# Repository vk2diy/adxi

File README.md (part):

# adxi - ADX Improved

[ADX](https://github.com/WB2CBA/ADX) is an abbreviation for Arduino Digital Xceiver, a project emphasizing simplicity and Arduino hardware creating a [direct-conversion receiver](https://en.wikipedia.org/wiki/Direct-conversion_receiver) focused on [digital modes](http://www.arrl.org/digital-data-modes).

The ADX project was based upon firmware by [JE1RAV](https://github.com/je1rav/QP-7C) extending on original work by Burkhard Kainka (DK7JD) ([original German](https://www.elektronik-labor.de/HF/FT8QRP.html), [English translation](https://www-elektronik--labor-de.translate.goog/HF/FT8QRP.html?_x_tr_sl=auto&_x_tr_tl=en&_x_tr_hl=en-US&_x_tr_pto=wapp)).

This (very distant!) fork of ADX is called __adxi__ (or "ADX Improved") with the following major changes:
 * __abandon simplicity as a design philosophy__ since it limits our feature set and understanding
 * __improved design documentation__ to facilitate learning
 * __restores access to the project for modern KiCad__
 * __integrate known bug fixes__
 * __operates from a single USB-C cable__ replacing the need for an MCU programming cable, a power cable, an audio input cable, an audio output cable, and a host computer sound card.
 * __USB-C power supply__
 * __full computer control__ (remove buttons/blinkenlights interface)
 * __improved filtering__
 * __SWR, forward power and reverse power metering__ for debugging, safety and performance analysis
 * __supports more amateur bands__: 70cm/2m/10m/15m/17m/20m/30m/40m/60m/80m/160m/630m/2200m
 * __use of modern surface mount components__ for repeatability
 * __using platformio__ to manage the firmware build and dependencies in a modern way

## Other projects
 * Same MCU
   * [ADX](https://github.com/WB2CBA/ADX) ($? / ATMega328P based / multiple bands with effort / LED blinkenlights/ CD2003GP direct conversion receiver)
   * [(tr)uSDX](https://dl2man.de/) (PE1NNZ and DL2MAN) ($50 / ATMega328P based / multiple bands with effort / small OLED / direct sampling)
     * Based on [µSDX](https://github.com/threeme3/usdx)
 * Fancy-pants MCU
   * [sbitx](https://github.com/afarhan/sbitx) ($150+ / RPi4 based / 8 bands preconfigured / large OLED) ([documentation](https://www.sbitx.net/), [designer website](https://www.hfsignals.com/index.php/sbitx-v3/)) (newer zbitx)
 * Discussion
   * [ucx discussion group](https://groups.io/g/ucx)

## Project scope

The project scope generally includes the following:
 * Main board
 * Late stage board modules (each for different frequency bands)
 * Assembly information
 * Design documentation
 * Debugging documentation

## Current status of this fork

The first boards have been received and despite issues have been verified as partly functional.

Completed:

 - [x] Updated schematic (Kicad 8)
 - [x] Layout
 - [x] Late stage module interface design
 - [x] Design and layout of first late stage module 
 - [x] Firmware building correctly under platformio
 - [x] Final design review
 - [x] Order boards

Underway:

 - [x] Board testing and bringup
   - [x] USB hub verified
   - [x] USB audio verified
   - [x] USB MCU module passthru verified
   - [x] Power stage testing completed (issues found; resolution proposed and partly bench tested)
     - [x] Design and order power stage fix board
     - [x] Receive and assemble power stage fix board
     - [x] Debug power stages with fix board
   - [x] Assemble, solder-configure and mount late stage module
   - [ ] Firmware authoring to verify remaining functional blocks (in progress)
   - [ ] WSJT software integration testing (in progress)
 - [ ] Test late stage module
 - [ ] Verify overall system functionality
 - [ ] adxi-1.3 main board revision - incorporating power stage fixes and other improvements.
   - [x] Created new board tree

## Update (2025-01-27)

 * Started on looking at the late stage module (LSM) board.
 * Isolated 40M band LPF on a new board by cutting the trace from the impedance matching.
 * Instrumented both sides with NanoVNA but did not get expected results from the 7th order Butterworth approximation with values produced by [classe2-calculator](https://github.com/vk2diy/classe2-calculator), namely:
   * Command line: `./classe2 -p 5 -v 12 -b 40m -t infinite --l1 7.755uh -m SI2304DDS`
     * ie. Power 5W, voltage 12V, band 40m, type infinite, Class E L1 value 7.755uH, MOSFET SI2304DDS.
   * Output for precise configuration (not used): `7th = (0.23% error, 18 parts): C1_lpf=132.00pF (220.00pF || 330.00pF) L1_lpf=0.93µH (2.2µH || 2.7µH || 3.9µH) C2_lpf=536.00pF (33.00pF + 33.00pF + 470.00pF) L2_lpf=1.5µH (2.7µH || 3.3µH) C3_lpf=536.00pF (33.00pF + 33.00pF + 470.00pF) L3_lpf=0.93µH (2.2µH || 2.7µH || 3.9µH) C4_lpf=132.00pF (220.00pF || 330.00pF)`
   * Output for approximation configuration (used): `7th ≈ (13.57% error, 7 parts): C1_lpf=150.00pF L1_lpf=1µH C2_lpf=470.00pF L2_lpf=1.5µH C3_lpf=470.00pF L3_lpf=1µH C4_lpf=150.00pF`
 * I had expected to see a rapid falloff at a specific frequency, like this modeled version: 
 * However, instead I obtained very different results.
   * __Test setup__. I did try to test with the extra ground cable shown with a red X, but removed it (ground loop). No substantial change.  
   * __Test result__. This remained fairly constant in all test configurations (with and without termination resistors, various ground configurations). 
     * What we can see here is:
       * __S21 Logmag__ in yellow (~"through signal attenuation") shows a downward slope within the target band (marker location) before a flat response through around 13MHz at which it begins to taper off fairly steeply until 17MHz at which point it begins to climb again.
         * Our expectation would have been "falling off a cliff" after the filter cutoff frequency and not recovering until very high frequencies due to self-resonance of individual components.
         * This is a head scratcher.
       * __S21 Q10__ in green (~"resonance or energy storage potential") is an undesirable feature in a low pass filter. However, we can see significant Q values around 5MHz and 9MHz.
         * This would seem to indicate there is a source of resonance within the test circuit which we have not identified. However, without other points of comparison it may be hard to determine how abnormal this is.
       * __S21 Rsh__ in cyan (~"shunt resistance") exhibits a small peak around the target frequency but is otherwise flat.
       * __S21 Phase__ in magenta (~"phase angle") shows the target frequency band exists within the middle of a smooth phase cycle. There is no information in this to suggest an issue. However, it is notable that the phase shifts at 13MHz where we see the attenuation increase markedly. From prior experience it is common and expected for phase change to align with the end of designed frequency ranges.
   * __Broader result__. This shows markers for the 40m as well as 30m and 20m bands. You can see the attenuation restores rather than decays with increasing frequency after 17MHz, which is unexpected.  
   * __Final test setup__. Note cut trace, solder points and 47 ohm series resistors at either end. No substantial difference. 
 * I am as yet uncertain why this is.
   * Hypothesis: Incorrect impedance matching.
     * Determination: Invalid. Added 47Ω resistors either site of the LPF DUT with no substantial difference observed.
   * Hypothesis: Low SRF components.
     * Determination: Invalid. All components in the filter, both small capacitors and inductors should have higher SRFs, at least in the 100-200M+ range at a minimum. However, they are not reported in the datasheet as they are not high end components. Even with low end assumptions this should provide a safe 'order of magnitude' (<10M vs 100M+) buffer.
   * Hypothesis: Poor grounding.
     * Determination: Possible but unlikely. Connecting the ground at both ends of the DUT (ie. ground loop) causes no significant shift in the VNA output, versus just one end.
   * Hypothesis: Poor calibration.
     * Determination: Used a range of new calibrations, stored calibrations and recalibrations but in no case did this alter the general frequency response.
 * __Next steps__
   * I put it away and will come back to it another day to look at the 30M and 20M LPFs - hopefully one of them works!
   * I could try adding a solid ground plane just to see the difference.
   * I could try fabricating a range of physically separate filters as standalone PCBs to simplify debugging (no test points and cutting traces is a real pain).

## Update (2025-01-19)

 * Been awhile since an update, but haven't been idle.
 * [Built, tuned and tested a 20m/30m/40m fan dipole antenna](doc/antennas/20m-30m-40m-fan-dipole) and got this running with an RTLSDR as a reference point in order to support further testing. Despite being barely 1.5m off the ground and threaded through foliage, it works! Signals have been received from most continents already. 
 * Updated test plan:
   - [x] Antenna system
     - [x] Build or acquire a viable antenna
     - [x] Verify with NanoVNA and attenuator for protection
     - [x] Verify with other radio hardware
   - [ ] The power amplifier
     * Power amplifier low pass filter, matching network and resonator
       * NanoVNA between the band-specific solder bridges (fresh board, none soldered closed)
     * RF choke
       * NanoVNA between the `PA-SUPPLY` and the nearby solder bridges (fresh board, none soldered closed)
   - [ ] MCU power amplifier drive PWM signal
     * Instrument appropriately with scope then test with custom firmware
   - [ ] MCU receive enable signal
     * Instrument appropriately with scope then test with custom firmware
   - [ ] The demodulator chip
     * Verify configuration straps with scope
     * Verify expected input signal is present with scope
     * Verify output signal is present with scope
   - [ ] The USB sound chip
     * Verify configuration straps and/or MCU control lines
     * Verify input from demodulator and channel mixing is present
     * Monitor computer audio through regular audio software
     * Try creating static if necessary by shorting low voltage leads
     * Verify static comes through to computer audio software

## Update (2024-12-04)
 * [Proposed test plan](kicad-pcbs/adxi/README.md) for resolving current state focused on iterative verification

## Update (2024-11-25)

 * Researched Linux-based serial data capture solutions with an eye toward [Wireshark](https://www.wireshark.org/) (which my brain still calls *Ethereal*!) and hit on [socat](http://www.dest-unreach.org/socat/), which is a spiritual successor to Hobbit's [netcat](https://sectools.org/tool/netcat/) that talks serial in addition to TCP/UDP and should therefore do the job.
   * It seems [very closely aligned functionality for logging devices under control by other programs was added in or before 2021](https://news.ycombinator.com/item?id=26604002)
   * To date I have been attempting to manually interact with the firmware using [minicom](https://salsa.debian.org/minicom-team/minicom) which is tedious.
   * It would be much better idea to create a test harness using [platformio](https://platformio.org/) to fire up [WSJT-X](https://wsjt.sourceforge.io/) and monitor the serial traffic to verify suspected interactions are taking place.
   * The best time to do this is immediately after a successful firmware upload, when the device firmware version, device name, etc. are all known.
   * Well written, such a test harness should:
     * Provide a high iteration speed platform for firmware testing and development
     * Catch changes to `WSJT-X`
     * Catch firmware bugs
     * Protect against firmware regressions.
     * Be portable to alternative, future MCUs (eg. `RP2040`).

## Update (2024-11-24)

 * [Stepping through manual clock control](kicad-pcbs/adxi/README.md) with the `SI5351` as a means to test the subsystem.

## Update (2024-11-22)
 * Got host system audio working.
 * WSJT initial errors all resolved
   * Audio interface errors resolved
   * USB serial interface errors resolved
   * Configuration errors resolved
   * Basic interface testing should now be possible.  The following error simply indicates the firmware is not responding as expected over serial (because we have been modifying it for testing).

```
Hamlib error: read_string_generic called, rxmax=4095 direct=1, expected_len=1
tcflush
write_block(): TX 3 bytes, method=2
0000    46 41 3b                                            FA;
read_string_generic called, rxmax=128 direct=1, expected_len=1
read_string_generic(): Timed out 0.200 seconds after 0 chars, direct=1
kenwood_transaction: read_string(expected=128, len=0)=''
kenwood_transaction: read_string retval < 0, retval = -5, retry_read=0, rs->rigport.retry=0
kenwood.c(628):kenwood_transaction returning2(-5) Communication timed out

kenwood_open: no response from rig
  2:kenwood.c(940):kenwood_open returning(-5) Communication timed out

  2:rig.c(7525):async_data_handler_stop entered
  2:rig.c(7555):async_data_handler_stop returning(0)
ser_close: restoring options
 1:rig.c(1301):rig_open returning(-5) Communication timed out

Communication timed out
Communication timed out
 while opening connection to rig

Timestamp: 2024-11-21T23:32:09.208Z
```
 * Turned out that even when dropping the effectively original serial handling code in place, the same error persisted.
   * This lead me to believe that there was some sort of timeout going on; perhaps in the I2C communication with the clock generator chip.
     * I tried uploading the same firmware to an MCU module with no hardware connected and obtained the same result; this was semi-confirmatory.
     * I instrumented the code by hand to obtain an understanding of where the latency was occurring.
     * After re-enabling `Serial.setTimeout(4)` things sped up.
   * I tried going back to the assembled board with this revised code to see if WSJT would initialize correctly.
 * WSJT now starts with no error! This is a pretty good milestone for further work. 

## Update (2024-11-20)
 * Went to test the [WSJT](https://wsjt.sourceforge.io/) integration and found my kernel doesn't have audio, wasted most of a day rejigging Gentoo packages and kernels (to be fair, upgraded almost everything on the system to latest and overcame some rustic and pythonic meta-situational transgressions)

## Update (2024-11-19)
 * Power stage fix board [fully debugged](kicad-pcbs/adxi-1.2-powerfix-1/), plugs in and works from USB-C
 * Firmware can now be uploaded and tested with no bench supply
 * Modified platformio configuration to get firmware uploads reliably working 

## Update (2024-11-11)
 * Began rewriting firmware, made gross simplifications, probably broke some stuff, and found another hardware bug.
 * Designed and ordered a power stage fix board. This should resolve the issues detected to date.   

## Update (2024-11-10)
 * [Bench testing](kicad-pcbs/adxi/) of the switchover part of the proposed power solution did not go according to plan, despite attempting two different combinations of Schottky diodes in a passive configuration, adding resistors and generally investing time.
   * The final perspective was that the issue could be the components themselves, could be the topology or could be a property of the bench supply channels when simultaneously applied to a circuit (various earthing options were tested).
   * The conclusion was to move to an active switching topology using a power MOSFET in a standard package size. This will disconnect the early stage supply once the regulated supply becomes available.

## Update (2024-11-09)
 * A [very busy week testing](kicad-pcbs/adxi/). 
   * Issues found in the power stages were numerous.
     * First there was a topology error in the USB power, mostly due to lack of personal dilligence in critically evaluating the datasheets, but also inexperience with USB power.
       * I am confident this should be resolved in the next revision or in a fix.
     * Second the boost converter had huge issues
       * First it was missing capacitance which was actually critical (unlike bulk output capacitance which may often be removed or reduced, high frequency capacitors are very important for stable boost conversion)
       * Second the inductor was oversized, as the datasheet simply suggested a range and I'd picked the larger end. Well, turns out there's a way to select these and I should have picked the middle to low end.
     * Third the unstable boost converter output with huge 75V swings was probably responsible for burning itself out, but also it was responsible for making the subsequent 12V regulator fail. Thankfully I was able to demonstrate that as soon as power was cut, however, the capacitor (added) was able to feed the 12V regulator and achieve perfect output.
   * None of these issues are critical, all can be resolved by power bypass or modification.
   * A potential fix board has been generally designed, but firmware testing to allow the evaluation of other functional blocks will proceed before an order is placed, just in case we have other issues and it may be more useful to redo the board as a whole.
   * Once this has been done, the new problem of testing the late stage module begins, which will no doubt involve some pretty NanoVNA graphs. I might cut one board to segment it in to functional blocks so that each can be characterised independently. This will not cause any loss of boards, because after testing is complete the board can be solder-configured for an alternate band (each initial late stage module supports 20m/30m/40m bands, but only one at a time, and I had 20 made for only 10 radios).

## Update (2024-11-05)

 * Boards arrived yesterday!
 * A [detailed log of debugging is available here](kicad-pcbs/adxi/)
 * Currently there is an issue with the USB power circuitry which I am working to resolve. It seems I made a mistake on this part of the design due to inexperience.
 * Bypassing that supply with a bench supply results in correct USB connectivity to all devices, which is very promising and quite rewarding given this is my first USB device.  
 * Probably, this means I can use the current boards by adding some external components, which have been ordered.
 * Further testing continues.

## Update (2024-10-24)

 * Finally ordered the boards, final versions as follows.  
   * Delays were mostly due to the need to update [classe2-calculator](https://github.com/vk2diy/classe2-calculator) to replace portions deemed inappropriate during DFM review and other matters taking my time.
   * I expect to receive the boards in a couple of weeks... looking forward to testing!

## Update (2024-10-03)

 * Quite a lot of progress.
   * [classe2-calculator](https://github.com/vk2diy/classe2-calculator) (pronounced "classier calculator") is reaching a fairly mature state with some very useful output.
     * Three power amplifier topologies are support: `-t infinite`, `-t finite` and `-t inverse`.
     * Three matching network topologies are supported: `-M l`, `-M t` and `-M pi`.
     * 1st-7th order low pass Butterworth filter networks are supported, these are automatically generated for all orders.
     * In all cases, practical approximations using standard component values are generated and ranked in descending order of accuracy along with part counts.
   * Late stage module
     * The late stage module has been redesigned with the new calculations.
     * Upon advice, the antenna tuning features have been dropped.
   * Main board
     * The main board has been redesigned as v1.1 and subsequently (underway) as v1.2
     * When the v1.1 was ordered, a number of issues were uncovered:
       * Component selection: overpriced components, unavailable components and undue component quantities
       * Double-sided assembly: one of the key components that is unrealistic to manually assemble is the USB-C port which had been placed on the underside. This however needs to move to the top side for process reasons.
       * In order to facilitate the above, a hole must be cut in the board for the MCU to MCU USB-2 interface port cable, since it cannot be on top of the board.
       * Thankfully some component upgrades (1000uF caps) and consequent board space downsizing has shown there is probably *just* enough space to make this happen.

   * I will not be focused on this project for a little while due to other commitments but will finish it ASAP.

## Update (2024-09-18)

 * __Still working on the [novel Class E component calculator tool](https://github.com/vk2diy/classe2-calculator)__. Turns out there's a lot of background to the evolution of the physics equations and AC circuit theory is a bit different to the DC stuff I'm used to, so this is taking awhile.
 * __Discovered another component concern__, this time Zener Diodes. 
   * Basically due to the difficulty of finding high voltage rated components the approach of using zener protection had been put forward. This is not particularly common in resonators, and probably for good reason.
   * Further research revealed the reason why.  So it seems that the use of Zener Diodes creates an increase in effective shunt capacitance (somewhat similar to the output gate capacitance or `C(OSS)` of a MOSFET) which effectively works in parallel to the shunt capacitor `C1`.
   * The previous zener diode was selected for as low a voltage as possible, but this is not a good look, particularly when using multiple zener diodes in parallel (the design had three).
   * Apparently, the higher the zener diode voltage rating, the lower the capacitance, because:
     * Depletion region width: As the voltage rating of a zener diode increases, the width of the depletion region in the PN junction also increases, and the wider depletion region results in a lower capacitance, as capacitance is inversely proportional to the distance between charge carriers.
     * Doping levels: Higher voltage zener diodes typically have lower doping levels. Lower doping leads to a wider depletion region and thus lower capacitance
.
     * Junction area: For a given power rating, higher voltage zener diodes often have smaller junction areas. A smaller junction area results in lower capacitance.
     * Reverse bias effect: As reverse voltage is applied to a zener diode (before breakdown), the depletion region expands further, reducing capacitance.
     * Higher voltage zeners operate at higher reverse voltages, leading to lower capacitance.
     * This relationship can be expressed mathematically as $$C = \frac{K \times D^4}{(\rho V_C)^n}$$ or the Unicode equivalent `C = (K × D^4) / (ρV_C)^n`
       * `C` = Capacitance
       * `K` = Constant
       * `D` = Junction diameter
       * `ρ` ($\rho$) = Material resistivity (related to doping)
       * `V_C` ($V_C$) = Voltage across the junction
       * `n` = Exponent (typically around 0.5) 
     * As the voltage rating (`V_C`) increases, the capacitance (`C`) decreases.
     * Once the zener reaches its breakdown voltage, the capacitance tends to stabilize and doesn't change significantly with further increases in current.
 * __Discovered some low-voltage components__.
   * Certain components will be swapped out for higher voltage equivalents.
 * __Discovered less than ideal diode selection__.
   * Diode switching speed in the forward and reverse power sampling circuit was identified as a concern.
   * I have done a [write-up on this](doc/swr-and-power-metering)
 * __Discovered topology error__.
   * Through a manual review, discovered not one but two topology errors in the late stage modules.
   * One error was to do with the overall topology across the main board interface.
   * One error was to do with the ordering of resonator components (`L2`/`C2` inverse).
   * The first prototype late stage module schematic has been updated to reflect the correct topology.

## Update (2024-09-11)

 * No update for almost a week, but I have been busy! The design review has revealed a large number of issues requiring resolution.
 * __Two full days were spent creating and enhancing new Class E calculator software__.
   * This decision was prompted by the revelation that repeatedly running existing third party software was an inefficient means to explore the solution space and certain concerns were raised regarding ambiguities in the algorithm, inputs and outputs for third party tools. No final tool was created however a lot of functionality was explored, including:
   * The generation of basic Class E circuit values.
   * The generation of matching networks in both "L" and "Pi" configurations.
   * The storage, retrieval and referencing of band information, transistor information, capacitor and inductor information.
   * Efficient caching systems for achieving faster reslts than naive depth-first search in the solution space.
 * __Development of the tool put on hold temporarily, and to assist with verification a number of existing third party tools were surveyed__.
   * The conclusion of the existing software survey was that much existing (pre-SMD) software is sub-optimal for a modern SMD-based device design use case:
     * Often the software is produced by HAM hobbyists to scratch and itch and does not meet broader requirements.
     * A common shortcoming was the explicit assumption of the use of hand-wound coils and the provisioning of coil-winding instructions rather than SMD component selection information.
     * Another shortcoming was the use of imperial measurements (no metric support).
     * Another shortcoming was the use of simple algorithms where more advanced information and methods are now available. For example, it is generally impossible with most tools to model the use of a given circuit with anything but a 50% duty cycle.
     * The main and overwhelming shortcoming was a critical lack of design documentation, specifically including an explanation of which algorithm was in use, and for what purpose, informed by which literature, etc. The majority of HAM-grade tools just provide hand-wavey references to *Sokal*, *NM0S*, and it has been shown that the latter incorporate circular references of dubious or limited connection the broader scientific literature. This is just not a good basis for moving forward with a proper understanding of the design space.
 * From a practical standpoint:
   * __Transistor selection was shown to be bad__. The transistor somewhat arbitrarily selected has proven insufficient for the application and thus will be replaced. While the power handling was excellent, certain aspects of its design (in particular output capacitance) were shown to be far in excess of practical for this application. Currently it seems the preferred replacement citing availablity, cost and modeling will be the `SI2304DDS`.
   * In terms of design verification, education and tuning, __current sensing would be very useful__.
     * Specifically, the ability to sense current in order to visualize the switching action of the Class E Power Amplifier primary switching device across input drive signal, load current and load voltage in order to verify the primary properties of the Class E Power Amplifier are in tune with the required characteristics, ie. zero voltage and zero current at the time of switching.
     * According to various sources ([TI](https://www.ti.com/lit/eb/slyy154b/slyy154b.pdf), [Analog Devices / Linear Technology](https://www.analog.com/media/en/technical-documentation/app-notes/an-105fa.pdf), [Renesas](https://www.renesas.com/us/en/document/apn/current-sensing-low-voltage-precision-op-amps), [Bourns](https://www.mouser.com/pdfdocs/bourns_n1702_current_sense_accurate_measurement_appnote.pdf), [Mouser/Microchip/Vishay](https://www.mouser.com/pdfDocs/microchip-vishay-current-sensing-whitepaper.pdf) and [ElectroicDesign](https://www.electronicdesign.com/technologies/power/article/21806322/electronic-design-using-resistors-for-current-sensing-its-more-than-just-i-v-r)) and a cursory review of lab equipment available for current sensing with oscilloscopes, plus some prior experience building current sensing circuits within boards using op amps, __it seems that it would be desirable to provide a measurement test point across a shunt resistor specifically for the provisoning of current measurement__.
     * Not having had the need for higher frequency measurements in the past, __my oscilloscope is limited to 70MHz which the following calculations show is perhaps just within the recommended range for this purpose__. For the higher frequency bands, this sampling and verification strategy will certainly run in to issues with my current test equipment.

| Band | Frequency | Nyquist | Practical Rate (2.5x) | Recommended Rate (3-5x) |
| ---- | --------- | ------- | --------------------- | ----------------------- |
| 20m  | 14 MHz	   | 28 MHz	 | 35 MHz                | 42-70 MHz               |
| 30m  | 10 MHz    | 20 MHz  | 25 MHz                | 30-50 MHz               |
| 40m  | 7 MHz     | 14 MHz  | 17.5 MHz              | 21-35 MHz               |

 * From a theoretical standpoint:
   * It was found that Class F and Class E/F circuits are sometimes mislabelled as Class E in software and this should be kept in mind.
   * The generation of Class F and Class E/F could be a rational decision for the analysis software.
   * It seems *critical* to actually visualize the actual switching-time voltage and current in order to fully comprehend and verify a Class E implementation, thus hardware must be designed to facilitate.
   * The degree to which different component blocks interact or are operation or replaceable should be more thoroughly investigated. For example:
     * Many source suggest the L1 RF Choke should be 10-15x L2 (resonator inductance) but do not further specify tuning.
     * Some sources suggest the L1 RF Choke can be larger than specified without incident, thus a common large inductor might be selected to cross all bands.
     * L1 (RF Choke) is apparently possible to replace with a "finite DC feed inductance" (FDI) and this is apparently well known and desirable at higher frequencies, eg. our targeted 70cm.
 * Next steps:
    * It now makes sense to spin the emergent calculation tool off in to its own tool which can be managed separately
    * After that is in a state of relative verification (re. generates values that generally concur with alternative calculators, includes reasonable defaults, provides useful output) then the component values will be recalculated for the initial late stage module board
    * The late stage module will be modified to include a current sense resistor and test point explicitly to facilitate the visualization of current information on the oscilloscope to demonstrate and tune the Class E circuit operation

## Update (2024-09-05)

 * Improved prototype late stage interface module for 20m, 30m and 40m bands
   * Correct rather than vague geometry
   * Correct orientation
   * Inclusion of RF choke
   * Inclusion of Sokal `C1` capacitor
   * Silk screen labels
 * Built-in antenna tuning
   * Based on a series of SMD-fixed elements with a solder-bridge enable
     * This should allow for reasonable tuning without the need for a separate antenna tuning system

## Update (2024-09-04)

 * Add mount point dimensions
 * Updates to silkscreen, including a "what it does" description and MCU labels visible on all pins
 * Significant updates test pads (preferred compact format for oscilloscope attachment, add more `GND` points, reposition a few pads)
 * Add 3D model of Arduino Nano from [over here](https://github.com/g200kg/kicad-lib-arduino) for demonstrative visualization purposes
 * Revisit layout for more cost effective vias (0.3mm vs 0.2mm)
 * Specify (and order) standoffs and cables
 * Moved out late stage schematics (done ages ago) to a separate directory in preparation for late-stage module PCBs
 * __Layout complete! This is version 1.__
 * Bullet point design review to date:
   * Total part-time design time was about 4.5-5 weeks. Actual design time maybe 2 weeks.
   * Initial estimate of "maybe one week" vs actual time investment of 2 weeks and calendar time investment of 5 weeks off by around 100%/500% (not a bad guesstimate!) ... 
     * Learning: Next time multiply the optimistic estimate by five for a real calendar time estimate.
   * Learned a *lot* of basic RF and radio design - both areas totally new to me - including:
     * Which stages require frequency-specific considerations (almost all of them, thus a combined [late stage interface](doc/late-stage-interface) incorporating parts of the Class E Power Amplifier and the band filter made sense, this being an architectural distinction from the previous project)
     * The various classes of amplifiers and detail regarding [Class E Power Amplifier design](doc/class-e-pa)
     * [How to design band-specific LPFs](doc/multi-band-lpfs) and why SRF is important
     * [How to get power from USB](doc/power-supply) and negotiate different power levels, without relying on the MCU module for the same
     * How to on-board a [USB hub](doc/usb-hub)
     * How to on-board a [USB audio chipset](doc/usb-audio-chipset)
     * How to [combine audio channels in hardware](doc/audio-summing)
     * [How to implement SWR, forward power and reverse power metering](doc/swr-and-power-metering)
     * The design history and AM-side configuration of a major family of [receiver chipsets](doc/receiver)
     * Why the old HAM radio trick of building your own coils is a pain in the ass but nonetheless useful to understand
     * A bunch about [antenna tuning hardware](doc/antenna-tuning)
     * Roughly how to use a vector network analyzer and link it with Linux software to characterize an antenna system, filter system, etc. with a frequency response curve
   * Also learned some better fundamentals including:
     * More of a decent background on available filter topologies (usually I just copy whatever's recommended)
     * How to torture AI in to giving you insights in to aspects of electronics design you have no clue about
   * Also came up to date with a few ecosystem state of play issues regarding KiCad 8 library management, fabrication partner file format preferences, etc.
 * Outstanding items
   * No idea if this will work, rather than attempting to roll in a frequency sweep / filter-characterization feature using the spare channel of the programmable clock generator I thought it was best to just order one revision and get things working.
   * Late stage boards with band-specific hardware still require layout
     * Perhaps first produce one popular band so that we can validate the overall design before investing in the others
     * The 20m band has been selected as the band to go for, based upon [WSPRNet Activity](https://www.wsprnet.org/drupal/wsprnet/activity) which is reporting the following bands have the highest recent activity levels:
       * 20m (675× contacts)
       * 40m (540× contacts)
       * 30m (437× contacts)
     * Made an early-stage prototype with solder-selectable support for all three bands 
   * Ordering
   * Post-ordering
     * Further firmware review and development
     * Try to plan out a test process for each block

## Update (2024-09-03)

 * Add silkscreen graphics
 * Add four M3 mounting holes with screw head footprint indicator silkscreen
 * Improve certain footprints
 * Simplify power supply to USBC only
 * Complete layout and DRC. (Also [discover and report DRC bug in KiCad](https://gitlab.com/kicad/code/kicad/-/issues/18642).)

## Update (2024-09-02)

 * Remodeled and improved [receiver chip](doc/receiver) [power filter](doc/filter-models/cd2003-supply-low-pass-filter).
 * Changed [stereo to mono audio summing to op-amp based](doc/audio-summing) (despite probable functional futility thereof since this is sourced locally) as theoretically this results in a cleaner output for an extremely nominal cost, and integrated the correct output bias line.
 * Found, reported and worked around [some](https://github.com/TousstNicolas/JLC2KiCad_lib/issues/77) [bugs](https://github.com/TousstNicolas/JLC2KiCad_lib/issues/76) in an [upstream library tool](https://github.com/TousstNicolas/JLC2KiCad_lib).
 * Executed most basic layout and verified all components fit in the allocated board space.

## Update (2024-09-01)

 * Specified the majority of schematic components still lacking footprints
 * Reconsider [receiver chip](doc/receiver) associated circuitry using a plethora of datasheets from chips in this family.
   * Learn more about the benefits of DC isolation for mixed AC/DC ICs.
   * [Model RF LPF](doc/filter-models/cd2003-rf-low-pass-filter).
   * Update peripheral circuitry to reduce cost and improve outcomes.

## Update (2024-08-29)

 * Detailed pin-wise documentation of MCU signals
 * Altered proposed PA schematic to show logical flow (top left to bottom right) with the proposed abstraction (*Sokal* flows "backwards" with respect to preferred schematic convention)
 * Completed crystal selection and load capacitance calculation for timer circuit (25MHz@12pF, 2x18pF)
 * Investigated frequency-specific questions regarding the MCU PA drive PWM line pullup, in particular to support 70cm frequencies, concluding no pullup is best (rely on MCU to set state, conserve power when operating in lower frequency bands, one less component)
 * Updated `TUSB321` power delivery chipset interface to remove mode-irrelevant pins and configuration.
 * Updated forward power, reverse power and standing-wave ratio (SWR) sensing schematic to provide better matching of voltage divider output to MCU ADC input range
 * Revised schematic for legibility, removed certain spurious elements
 * Reviewed original firmware

## Update (2024-08-28)

 * Completed audio summing for USB audio chip output
 * Wrapped frequency-response significant portions of the power amplifier (PA), the low pass filter (LPF) and antenna (ANT) interface in to a single unified prototype physical interface
   * Began to compare proposed component count board space with potential physical designs
   * An early stage prototype is shown in 3D and schematic views, based upon 3x2.54mm pin headers
   * Began to write this up as [doc/late-stage-interface](doc/late-stage-interface)

## Update (2024-08-27)

 * __Substantial amount of additional schematic work and documentation__
   * [USB hub](doc/usb-hub)
   * [Power supply](doc/power-supply)
   * [SPI level conversion](doc/spi-level-conversion)
   * Added many test points
 * More component footprints and models
 * Finished off some missing parts in earlier areas of the schematic
 * Readying to refocus on the new joint PA/LPF module mechanical and electrical interface design, after which layout should be straightforward

## Update (2024-08-24)

 * Power supply path further implemented
 * USB-C unified port for all purposes largely implemented including power delivery
 * USB hub configured
 * USB audio configured
 * New parts and footprints created
 * Minor amount of layout work

## Update (2024-08-22)

 * __New power supply mostly implemented__ with dual inputs, either USB-C PD or ~12-36V DC IN
   * Precise nature of fallback for USB-C power chain yet to be determined re. 1.5A negotiation failure
 * __Plan is now to onboard both the digital audio interface and a USB hub__ in order to facilitate the use of a __single USB-C cable to the host__ replacing six elements:
   * Batteries and a charge controller for mobile operation
   * DC-IN for fixed operation
   * Audio in
   * Audio out
   * Either an onboard module or external sound card for audio interfacing
   * Programming cable
 * It will be necessary to draw the schematics for these.

## Update (2024-08-21)

 * Early stage band module schematic proposal. 
   * The primary difference to the prior ADX design is that the physical module will include portions of the power amplifier (RF choke, Sokals' `C1`, resonator) in addition to the low pass filter (LPF).
   * This is thought to make sense because:
     1.  All of these elements were found to require adjustment when considering the revised design's wide aggregate proposed band capabilities; and
     2. "Getting it right first time" may not be either (a) rational expectation; or (b) therefore a cost-effective development trajectory.
   * In other words:
     * I don't trust myself enough to commit to a PCB run where these aspects cannot be further tuned.
     * By putting in the thinking up front to reduce my own development cost, it should also make the process of extending or tweaking the design further by others much easier.
   * Outstanding questions:
     * Since the modular portion includes all of the last stages of the transceiver, it would thus logically include the antenna connection
     * Since the antenna connection is something that people may want in various formats to suit various wavelengths and usage scenarios (IPEX, BNC, SMA) and some of those physical interfaces are not designed for longevity, and the "tiffin" approach will facilitate both vertical layering and improved EMI, it might make sense to zoom out to consider whether or not the antenna should be part of that module or signals should be routed back to the main board before connecting to the antenna.
       * Layering up makes sense because an antenna connection on top of the system would be a logical position, batteries are heavy and could fit below, and minimizing the overall inter-module routing of RF signals would be desirable.
       * Routing back makes sense because fewer modules are required and the specific modules would presumably work out cheaper. 
 * Design conclusions:
   * Don't bother with a screen, instead rely on the computer to provide status information.
   * Don't bother with a battery or charge controller, instead rely on an external USB power bank when mobile.
     * For the purposes of easier mobility and the fact that many laptops or embedded systems cannot supply anything near 1A on their USB ports it may be useful to obtain 5V nominal supply from one port and data from another port, ie. have two USB ports, one for MCU interfacing and one for power delivery.
     * For the purposes of maximum transmit power draw (~1A @ 5V) versus many USB supply limits (~900mA) and safety buffering, it may be useful to add a supercapacitor to the main board.
       * This could also allow switching between power sources without loss of operating state and configuration
     * Given that we are sailing so close to maximum draw it seems a tested solution would be desirable. A shortlist of potential integrated solutions includes:
       * TI TUSB312 - [Chinese](https://wmsc.lcsc.com/wmsc/upload/file/pdf/v2/lcsc/1809072322_Texas-Instruments-TUSB321RWBR_C139392.pdf), [English](https://www.ti.com/lit/ds/symlink/tusb321.pdf) @ $0.34
       * ST STUSB4500QTR - [English](https://wmsc.lcsc.com/wmsc/upload/file/pdf/v2/lcsc/2106070703_STMicroelectronics-STUSB4500QTR_C2678061.pdf) @ $1.29
       * ONSemi FUSB302 - [English](https://wmsc.lcsc.com/wmsc/upload/file/pdf/v2/lcsc/2304140030_onsemi-Fusb302mpx_C442699.pdf) @ $0.71
       * Cypress CYPD3177 - [English](https://wmsc.lcsc.com/wmsc/upload/file/pdf/v2/lcsc/2208051100_Infineon-Cypress-Semicon-CYPD3177-24LQXQ_C2959321.pdf) @ $0.81
     * Given that the TI chip is so much cheaper but they will all probably do the job I think it's worth moving forward with TI.
   * With increasing density comes decreased isolation and increased potential for electromagnetic coupling which is a double-edged sword.
 * Other developments:
   * Considering placing USB audio bridge, USB hub and port for MCU connection on board
     * This would allow programming and operation through a single port - no audio cables required
     * The only conceivable downside is, in a mobile scenario, USB power delivery capabilities of some host devices are limited
       * People can solve this themselves by using USB battery packs with built-in powered USB hubs
   * At this point, it sort of seems ridiculous to keep using the MCU as a module, but it is a pleasant eccentricity to preserve this design element and hard to match on price
     * Future versions could be released with newer MCUs, possibly mounted via adapter boards

## Update (2024-08-19)

 * Issues largely resolved with the PA choke.
   * Operating range was divided in to 3 band-groups (similar to resonator) and 2/3 completed with switching work yet to be done.
 * It seems that to obtain good values for `C1` (Sokal) it will be [necessary to recompute those at each end of the operating band for each resonator and choke selection](https://people.physics.anu.edu.au/~dxt103/calculators/class-e.php), and also to switch those when either PA or resonator change. If these figures work out, however, then confidence in the design should grow.
 * The fact that the Class E PA's RF choke, resonator, C1, and band-specific LPFs all require switching means it is probably best to redesign the group of adjacent passives as a single physical interface and module to support easier and more cost-effective experimental iteration.
 * This means the previous modularity scheme (ie. one of pluggable band-specific LPFs inspired by previous projects) is probably going to evolve to a higher component count, higher flexibility approach incorporating all of these functional blocks.

## Update (2024-08-18)

 * MCU output expansion added to drive switched PA resonator inductance and capcitance to achieve full band range
 * [Having issues](doc/class-e-pa/) identifying a sane strategy for an RF choke capable of the 70cm (450MHz) required
   * To this end, attempted to make at fabricating a coil for main RF choke but failed
   * Still keen to obtain an SMT solution

## Update (2024-08-15)

 * [Further work on power amplifier theory and component selection](doc/class-e-pa/)
   * We now have theoretically adequate SRF on inductor arrays for all bands
 * RF choke still needs a high SRF all-band solution but nominal values of near 220uF and an associated capacitor array have been chosen
 * Tiffin system added to potential footprint drawings

## Updated (2024-08-13)

Recent work:
 * More work on power amplifier
   * Three-mode RF choke inductor mostly completed (one tier to be re-specified)
   * Switchable capacitance calculated and to be added
 * Input of general dimensions of two boxes which have been selected as possible form factors. Have another idea to use this sort of thing as a modular approach: 
 * General cleanup of schematic

## Updated draft PCB (2024-08-10)

 * Further consideration of overall layout, switching placement.
 * It seems there will need to be a series-parallel array of RF choke inductors to cover the broad target frequency range.
   * This is not necessarily expensive, just complex.
   * There will also be at least one switchable inductor in the main RF choke.
 * Other additions:
   * I2C LCD pin header
   * Further antenna connector (MMCX)

## Updated draft PCB (2024-08-09)

This version adopts a band-module approach in order to reduce iteration cost.

The basic notion is that a 7x3cm module can be plugged in to provide band-specific low pass filtering.

There is space on the front of the PCB for three of these modules, and on the rear of the board another three modules. Modules are staggered to minimize the effects of electromagnetic coupling between modules and their terminals. Sockets are used on the board and pins on the filter modules in order to reduce the volume of metal present when less filters are connected.

## Initial draft PCB (2024-08-07)

 * Draft now changed, potentially to have pluggable LPFs instead of a monolithic all-band-onboard architecture
   * This requires the design of an interface for the same
 * Filter switching added

## Current documentation
 * Filters
   * [Bandpass filter model](doc/filter-models/bandpass-filter/) showing audio frequency bandpass filter
   * [CD2003 5V supply filter model](doc/filter-models/cd2003-supply-low-pass-filter/) showing power supply filtering for the radio receiver chipset
   * [DC blocking filter](doc/filter-models/dc-blocking-filter/) showing how capacitors block DC and their nominal frequency relationship
 * Schematic design notes
   * [Multi-band low pass filters](doc/multi-band-lpfs) showing various third party designs for multi-band LPFs and including notes considering practical aspects of the design problem.
   * [SWR and power metering](doc/swr-and-power-metering) discussing the planned approach to obtaining this information simply
 * Wireless protocols
   * *[The FT4 and FT8 Communication Protocols](doc/wireless-protocols/FT4_FT8_QEX.pdf)*

## ADX Original Project

### Features

 * ADX is a mono band (actually quad band) digital modes optimized HF transceiver that can cover four pre-programmed bands one band at a time by swapping Band LPF Modules.
   * It can work on 80m, 40m, 30m, 20m, 17m, 15m and 10m bands
   * It can operate on four of the most popular digital modes, FT8, FT4, JS8call and WSPR.
 * ADX supports computer control (CAT) by emulating KENWOOD TS2000 HF Transceiver over a 9600 8N1 serial link to control Band and Mode changes.

### Goals

The project was originally designed by [Barb (WB2CBA)](https://github.com/WB2CBA/ADX) ([original project website](https://antrak.org.tr/blog/adx-arduino-digital-transceiver/))  with the goal to design a simple HF Transceiver optimized for operating on Digital modes:
 - Simple to procure – meaning not effected by chip shortage
 - Simple to build – 2 modules, 2 IC’s and 4 Mosfets!
 - Simple to setup and tune – One simple calibration procedure is all needed.
 - Simple to operate – Plug in ADX MIC to soundcard MIC input and ADX SPK to PC soundcard speaker input and we are good to go with any digital modes Software.
 - Dirt Cheap – Costs less than 25$ to get all parts and PCB if we exclude ridiculous shipping costs!
 - Plug in a USB cable between ADX Arduino and your PC, Select Kenwood TS2000 with 9600bps,8,1 setup as your CAT rig and you will have CAT control on ADX!

It has since been built all over the world.

### Design

The original design was based on the following major physical modules:
 * Main ADX PCB
   * CD2003 radio chip
   * 74ACT244 buffer/line driver
 * Arduino Nano (ATmega328P MCU module)
 * Si535x clock generator module
 * uSDX LPF band module
 * External PC microphone interface (for sending received signals to the computer)
 * External PC speaker interface (for receiving encoded signals from the computer)

## Building the firmware

Firmware is managed through [platformio](https://github.com/platformio/platformio-core).

Rationale:
 - While excellent in its simplicity, Arduino IDE is generally inappropriate for long lived projects.
   - Why?
     - It has brittle dependency management
     - It relies on non-scriptable GUI actions.
     - It lacks modern features like unit testing, CI/CD, etc.

Result:
 - You will need to install either [platformio-core](https://github.com/platformio/platformio-core) (command line) or [platformio IDE](https://platformio.org/platformio-ide).

Benefits:
 - Notes about specific versions of specific libraries and compatibility are now a thing of the past.
 - The addition of future libraries, compilers, or tools is easy
 - Users become familiar with more modern, cross platform and professional grade approach to firmware development and management while working on personal projects

### Under platform-io core (command line)

Simply change to the source code directory and type `pio run`.

```
$ cd firmware
$ pio run
```

### Under platformio IDE

Open the project in the IDE then use the buttons provided.

## History

### 2024-08-07
 - First 'mostly there' release of Kicad v8 schematic and board design

### 2024-08-03

 - Forked, general cleanup and migrated to [platformio](https://github.com/platformio/platformio-core).
   - Previously Arduino IDE builds were the norm
   - Apparently the files had apparently not been opened since KiCad v4 ... KiCad is now at v8.0.4
 - Outstanding issues
   - KiCad has altered its library management so much that the old files will not import directly to v8.0.4
   - KiCad has improved its internal libraries so that external libraries for many parts are no longer required
   - KiCad has integrated the historic DigiKey library
   - The schematic is missing known PCB fixes not integrated but documented by the original author
   - The schematic uses a non-standard symbol for the MCU which is unhelpful
   - The schematic has a number of further errors making it suboptimal for introducing new students
   - The layout used a type of fill which is no longer supported by modern KiCad
   - The layout can probably be improved
 - Conclusion
   - Given the simple nature of the schematic it is better at this point to redraw the schematic and redo the layout, removing all previous KiCad 4 era files

### 2023-07-14

- Release band display bug fixes by Peter Petrov (LA7WRA) and Mark Culross (KD5RXT).

### 2023-06-10

- Cowtown Amateur Radio Club ADX Buildathon Construction Manual v1.5 by Richard Hinsley (W5ARH/VK2ARH)

### 2023-04-08

- SI5351 module pull up resistor fix added to build manual v1.4 by Richard Hinsley (W5ARH/VK2ARH)

### 2022-12-20

- Calibration procedure changed to protect EEPROM from R/W wear.
- Add zener diode PA mosfet protection from excessive SWR conditions.

## Contributors

### adxi project

 * VK2DIY

### ADX Project

 * [Barb (WB2CBA)](https://github.com/WB2CBA/ADX): Project conception and original design.
 * [Richard Hinsley (W5ARH/VK2ARH)](https://www.qrz.com/db/W5ARH): Buildathons, outreach and build documentation.
 * [Joerg Frede (DK3JF)](https://www.qrz.com/db/DK3JF): CAT and other software contributions.
 * [Peter Petrov (LA7WRA)](https://www.qrz.com/db/LA7WRA) and [Mark Culross (KD5RXT)](https://www.qrz.com/db/KD5RXT): Band display bug corrections.
 * [Burkhard Kainka (DK7JD)](http://elektronik-labor.de/): Initial FSK TX signal generation code - http://elektronik-labor.de/HF/SDRtxFSK2.html
 * [Jason Mildrum (NT7S)](https://www.qrz.com/db/NT7S): SI5351 Library - https://github.com/etherkit/Si5351Arduino
 * [Lajos Höss (HA8HL)](https://www.qrz.com/db/HA8HL): Inspiration for CAT code based on his TS2000 CAT implementation.
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
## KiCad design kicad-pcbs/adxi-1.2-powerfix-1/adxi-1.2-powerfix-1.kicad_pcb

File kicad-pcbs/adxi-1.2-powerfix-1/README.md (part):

# adxi-1.2-powerfix-1

## Timeline

 * Conceived: 2024-11-08ish
 * Designed: 2024-11-11
 * Ordered: 2024-11-11
   * Cost: $5 for 10 pieces of 2-layer PCB + $23.57 for surface mount and components = $28.57 for 10 boards, or $2.86 each
   * Shipping: $28.58
   * Effective cost: $5 each
 * ETA: 2024-11-21
 * Received: 2024-11-17 (morning) - ie. 6 days!
 * Assembled: 2024-11-17 (evening)
   * VBUS-IN pin and 12V-OUT pins must be clipped short by around 50% as they are not through-hole and the others are
   * Other pins may require some bending/re-alignment
 * Installation: 2024-11-18 (morning)
   * Proposed process:
     1. Remove `R80` (100K) beneath `VIN-OUT` pin. This has the effect of disabling existing boost conversion stage upstream connectivity from the 12V regulator.
       * Done
     2. Remove `L226` (22uH) east of below the `VDD-OUT` pin. This has the effect of disabling boost conversion stage resonance.
       * Done
     3. Remove `U8` (MT3608B) east of below the `VBUS` pin. This has the effect of disabling boost conversion entirely.
       * Done
     4. Verify pin alignment in all cases.
       * Done
     5. Solder in place.
       * First load solder on to the two non through-hole pins, ie. `VBUS-IN` and `12V-OUT`, because the first one is beneath an undercut and the second one also has reduce accessibility.
         * Done
       * Now tack down `VBUS-IN`. Verify the connectivity with a multimeter between the `VBUS-IN` pad on the fix board and the northern (inner) pad of the ferrite bead `FB6` at the `MCU`.
         * Done
       * Solder all through-hole pins from below.
         * Done
       * Finally solder the remaining pin, `12V-OUT`, to the pad. Verify the connectivity with a multimeter between the `12V-OUT` pad on the fix board and pin 1 on the mainboard regulator `U3`.
         * Done

## Test process

### Initial power tests

Rather than plugging the board straight in to USB-C it might be worth testing the power subsystems one by one before doing so, to prevent losing the soldering and assembly work and another board.

What can be realistically tested?

First of all we can test feeding 12V from the `GND` and `12V-OUT` pins on the fix board through to the regulator and see if the other power channels come up.

We will try 0.1A 12V for a short period and instrument 12V, 5V, and 3.3V during the test. If these all come up, then we know source power pass-through is working and should be able to plug in a USB source.

First, the power supply configuration will be programmed for 0.1 seconds in the test program `debugging/powertest` which activates the PSU's channel #2 for a short period and takes a PSU screenshot under load before shutting down.

A dry run resulted in the expected output.

After hooking up channel #2 as an input to the board, the oscilloscope channels need to be connected and set to trigger with input power. 

```
$ ./powertest
DP832 PSU
 - Status: OFF
 - Version: RIGOL TECHNOLOGIES,DP832,DP8C233203778,00.01.16
 - Self test: TopBoard:PASS,BottomBoard:PASS,Fan:PASS

Turning channels off... OK
Setting up channel #1
 - Voltage: 24.000V
 - Voltage limit: 24.000V
 - Voltage limiting: ON
 - Current: 0.500A
 - Current limit: 0.500A
 - Current limiting: ON
Setting up channel #2
 - Voltage: 12.000V
 - Voltage limit: 12.000V
 - Voltage limiting: ON
 - Current: 0.100A
 - Current limit: 0.100A
 - Current limiting: ON
Setting up channel #3
 - Voltage: 5.000V
 - Voltage limit: 5.000V
 - Voltage limiting: ON
 - Current: 0.500A
 - Current limiting: ON

Triggering channel 2 (12V) for test period
 - Enable
Saved screenshot_192.168.8.3_2024-11-18T07:02:51.png
 - Disable
```

Hrrm. Well the first run didn't trigger the scope or show any draw on the PSU screenshot.

A second attempt, leaving the channel on manually for a under a second resulted in an overcurrent condition on the PSU channel.

Let's increase the current to 0.3A, which was the level in the previous test scripts, and retry with the programmatic approach.

Same thing, no output, no capture.

Let's try increasing the time to one second or so.

Aha! We can see some draw at least. I wonder why the scope didn't trigger?

I tried switching it to real time and repeated, all the scope channels did move.

After changing the scope configuration (shorter time window, reset trigger level, change trigger to omnidirectional, etc.) I retried and it worked.

Needs to zoom out, clearly, but you can see the `VIN` input from the power supply is ramping up.

Zoomed out, retried.

And again... bang! We're in business.

Here you can see all channels have ramped up, although not yet stabilised.

And finally here is the full view of all power rails from zero to stable.

The conclusion is that, as expected, after performing surgery on the original board and connecting the fix board carefully we can confirm there is still expected and correct functionality obtained in terms of power system startup when powering the 12V rail directly from the fix board's output. The total time from power input to stable operation is around seven divisions of 20ms each, or 7x20 = 140ms.

### USB VBUS power test

The next most conservative test we can try is to directly power the USB `VBUS` input with 5V and a virtual USB2 VBUS current level of 0.5A with overcurrent protection enabled.

This test is intended to simulate the USB having been plugged in to a legacy peer device which does not support higher modes, such as 1.5A USB2 charging or USB3 power delivery (PD). With this approach we will limit the current to a practically conservative level and look to see whether or not sourcing power directly from the USB VBUS line without a compliant USB2 or USB3 device supporting higher current negotiation or provisioning results in correct startup.

What we would anticipate seeing is some level of power up, although the state indication output pins of the `TUSB321` device would not indicate high power availability, we should in practice still be able to use the whole system to some level, certainly the MCU and receive functionality, if not some sporadic or burst transmission as well. While we can't fully test those later-stage features, we will test that the power does come on and get distributed correctly across the board.

After an initial test proving this is the case, we should repeat the test a few times leaving the power on for slightly longer periods working up to 10 or 20 seconds and see if there are any thermal issues.

Should the test conclude with correct power and no thermal issues then we are should be in a relatively confident position to plug in a real USB device, without current limiting, and observe the results.

Let's modify the previous test script to power only the 5V channel, set that channel to come on for a short time, and rewire the 5V channel anode to supply voltage directly to the `VBUS-IN` pad on the fix board.

```
DP832 PSU
 - Status: OFF
 - Version: RIGOL TECHNOLOGIES,DP832,DP8C233203778,00.01.16
 - Self test: TopBoard:PASS,BottomBoard:PASS,Fan:PASS

Turning channels off... OK
Setting up channel #1
 - Voltage: 24.000V
 - Voltage limit: 24.000V
 - Voltage limiting: ON
 - Current: 0.500A
 - Current limit: 0.500A
 - Current limiting: ON
Setting up channel #2
 - Voltage: 12.000V
 - Voltage limit: 12.000V
 - Voltage limiting: ON
 - Current: 0.300A
 - Current limit: 0.300A
 - Current limiting: ON
Setting up channel #3
 - Voltage: 5.000V
 - Voltage limit: 5.000V
 - Voltage limiting: ON
 - Current: 0.500A
 - Current limit: 0.020A
 - Current limiting: ON

Triggering channel 3 (5V) for test period
 - Enable
Saved screenshot_192.168.8.3_2024-11-18T09:28:04.png
 - Disable
```

Very encouraging result! The `5V` input can be seen scaling up, and the `12V` can be seen beginning to scale up.

Obviously the startup time is slower due to the limited current available, but what we're seeing does indicate that the 12V rail is rising and the boost supply is working.

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
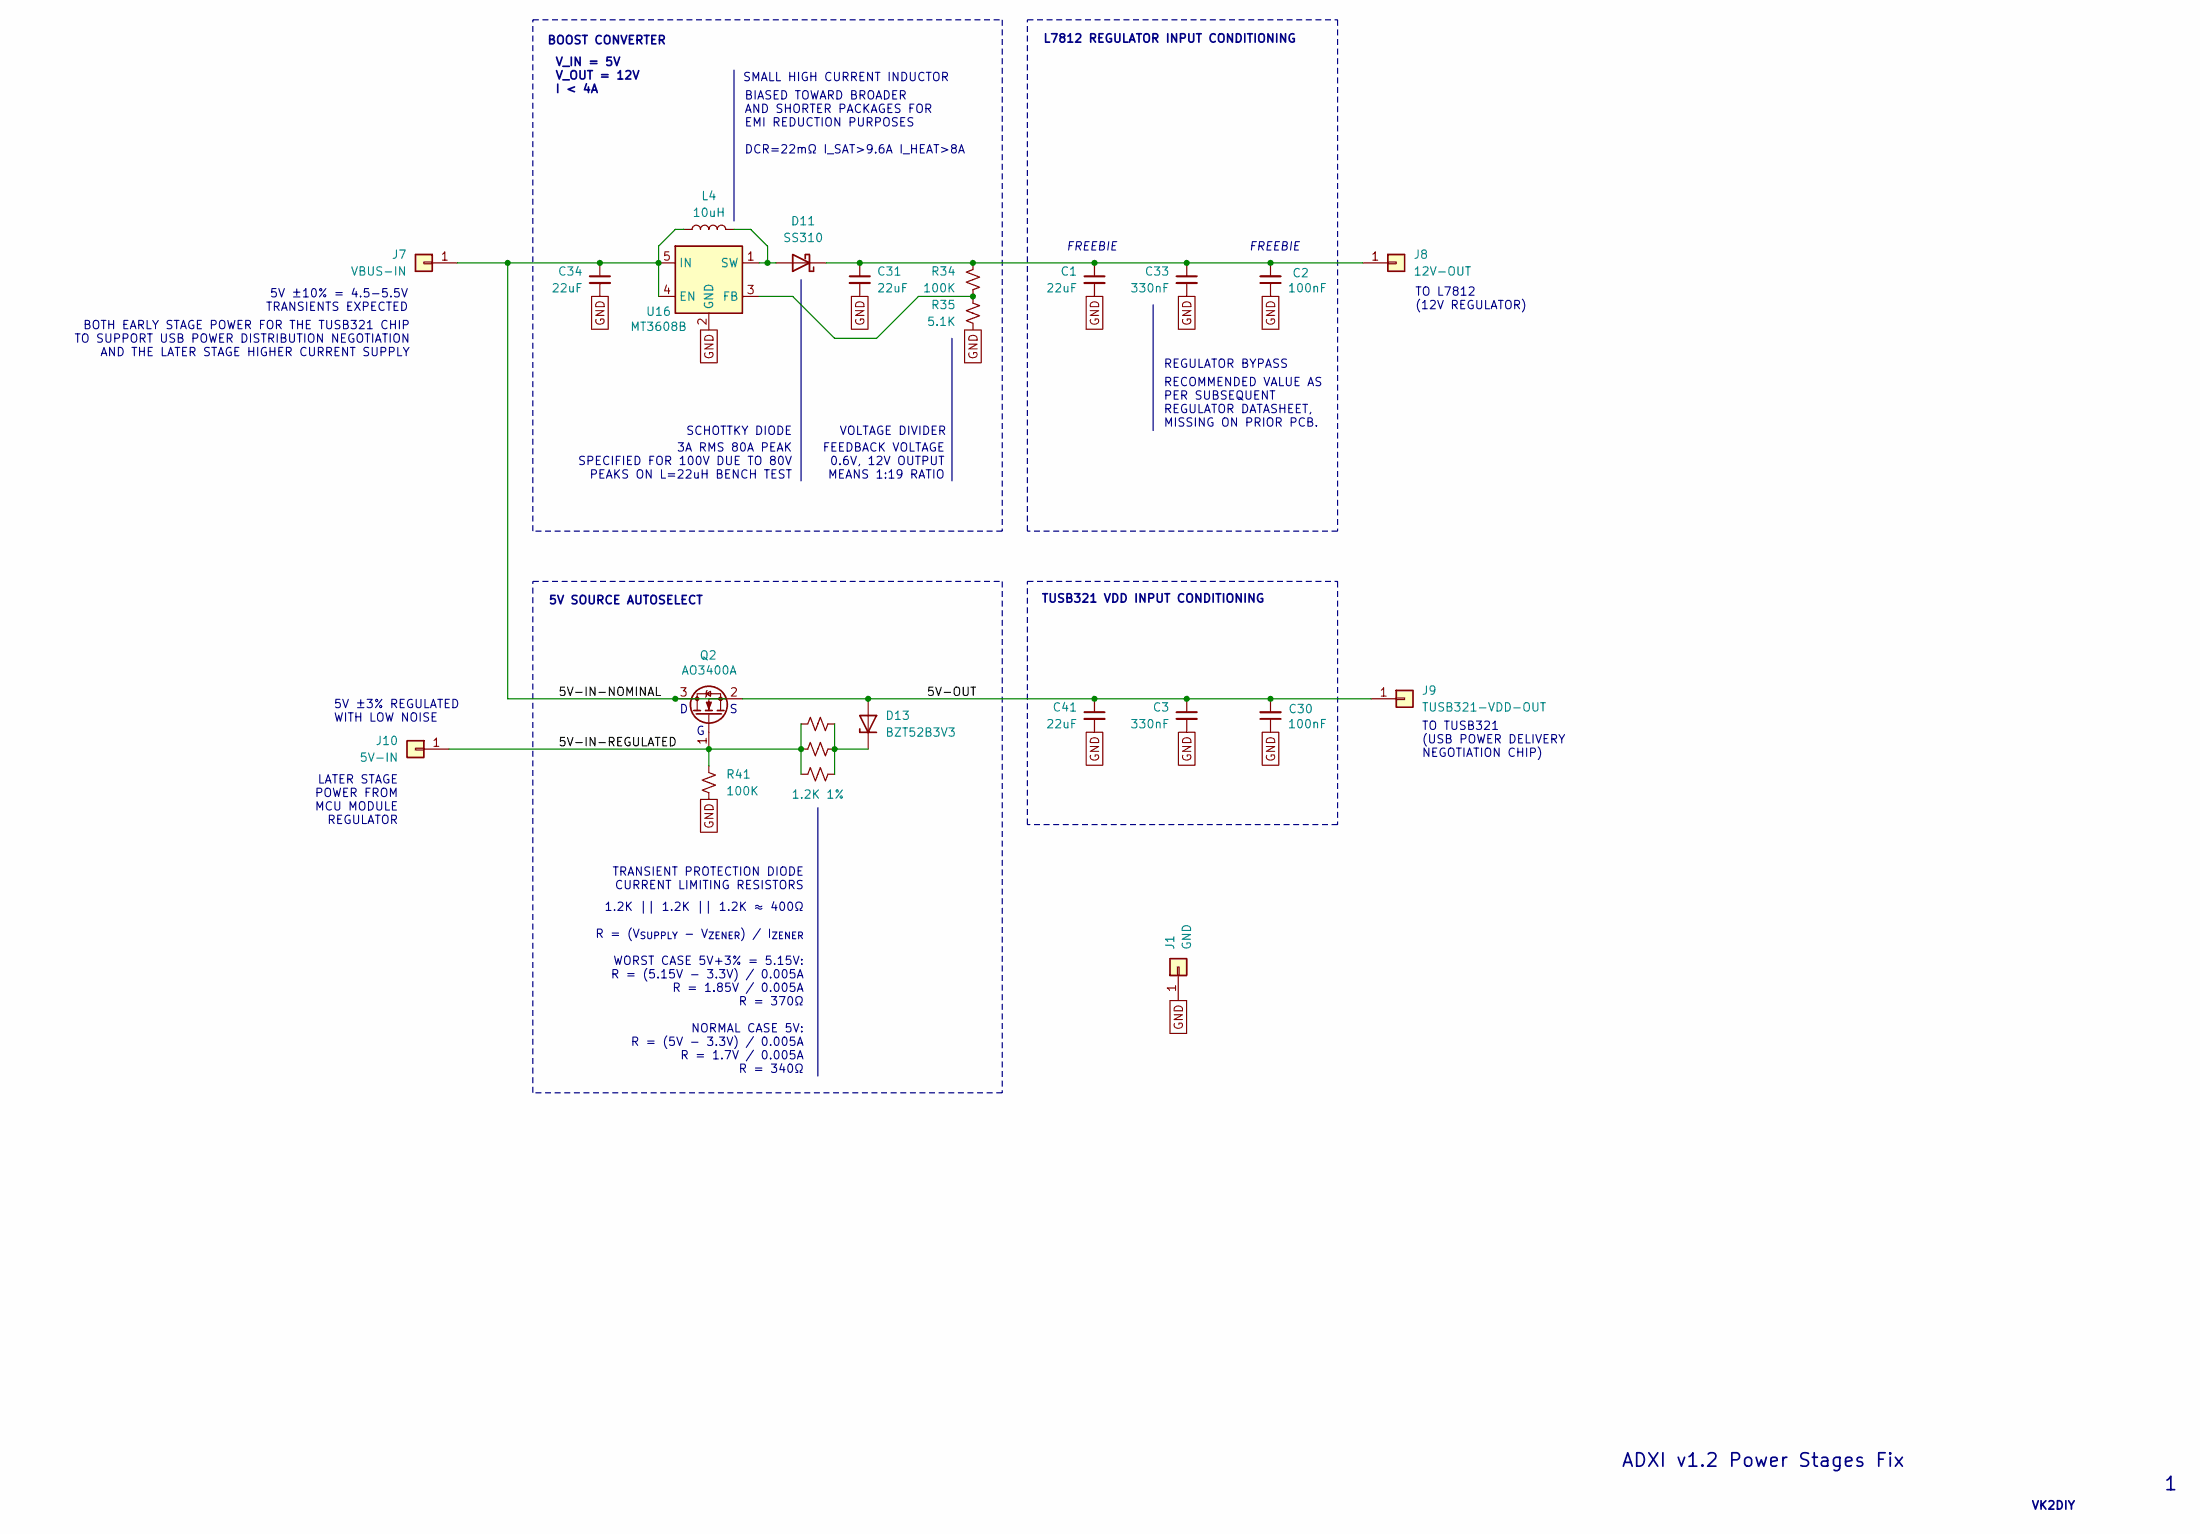
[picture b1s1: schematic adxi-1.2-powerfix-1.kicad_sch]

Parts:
C1, C31, C34, C41: 22uF; C_0805_2012Metric; MPN CL21A226MAQNNNE; LCSC Part # C45783
C2, C30: 100nF; C_0805_2012Metric; MPN CL21B104KCFNNNE; LCSC Part # C28233
C3, C33: 330nF; C_0603_1608Metric; MPN CC0603KRX7R9BB104; LCSC Part # C14663
D11: SS310; D_SMA; MPN SS310; LCSC Part # C7420364
D13: BZT52B3V3; D_SOD-123F; MPN BZT52B3V3; LCSC Part # C19077392
J1: GND; PinHeader_1x01_P2.54mm_Vertical
J7: VBUS-IN; PinHeader_1x01_P2.54mm_Vertical
J8: 12V-OUT; PinHeader_1x01_P2.54mm_Vertical
J9: TUSB321-VDD-OUT; PinHeader_1x01_P2.54mm_Vertical
J10: 5V-IN; PinHeader_1x01_P2.54mm_Vertical
L4: 10uH; IND-SMD_L12.6-W13.5; MPN FXL1350-100-M; LCSC Part # C526017
Q2: AO3400A; SOT-23; MPN AO3400A; LCSC Part # C20917
R34, R41: 100K; R_1206_3216Metric; MPN 1206W4F1003T5E; LCSC Part # C17900
R35: 5.1K; R_0805_2012Metric; MPN 0805W8F5101T5E; LCSC Part # C27834
R42, R43, R44: 1.2K 1%; R_0603_1608Metric; MPN 0603WAF1201T5E; LCSC Part # C22765
U16: MT3608B; SOT-23-6; MPN MT3608B; LCSC Part # C19189893

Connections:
/5V-IN-NOMINAL: C34.1, J7.1, L4.1, Q2.3 (D), U16.4 (EN), U16.5 (IN)
/5V-IN-REGULATED: J10.1, Q2.1 (G), R41.2, R42.1, R43.1, R44.1
/5V-OUT: C3.1, C30.2, C41.1, D13.2 (A), J9.1, Q2.2 (S)
GND: C1.2, C2.1, C3.2, C30.1, C31.2, C33.2, C34.2, C41.2, J1.1, R35.2, R41.1, U16.2 (GND)
unnamed: D11.2 (A), L4.2, U16.1 (SW)
unnamed: C1.1, C2.2, C31.1, C33.1, D11.1 (K), J8.1, R34.2
unnamed: D13.1 (K), R42.2, R43.2, R44.2
unnamed: R34.1, R35.1, U16.3 (FB)

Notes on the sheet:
FREEBIE
VK2DIY
SCHOTTKY DIODE
BOOST CONVERTER
FEEDBACK VOLTAGE 0.6V, 12V OUTPUT MEANS 1:19 RATIO
ADXI v1.2 Power Stages Fix
V_IN = 5V V_OUT = 12V I < 4A
REGULATOR BYPASS
3A RMS 80A PEAK SPECIFIED FOR 100V DUE TO 80V PEAKS ON L=22uH BENCH TEST
TO L7812 (12V REGULATOR)
TO TUSB321 (USB POWER DELIVERY NEGOTIATION CHIP)
VOLTAGE DIVIDER
5V ±10% = 4.5-5.5V TRANSIENTS EXPECTED
BIASED TOWARD BROADER AND SHORTER PACKAGES FOR EMI REDUCTION PURPOSES DCR=22mΩ I_SAT>9.6A I_HEAT>8A
LATER STAGE POWER FROM MCU MODULE REGULATOR
TUSB321 VDD INPUT CONDITIONING
TRANSIENT PROTECTION DIODE CURRENT LIMITING RESISTORS
L7812 REGULATOR INPUT CONDITIONING
1.2K || 1.2K || 1.2K ≈ 400Ω R = (V_{SUPPLY} - V_{ZENER}) / I_{ZENER} WORST CASE 5V+3% = 5.15V: R = (5.15V - 3.3V) / 0.005A R = 1.85V / 0.005A R = 370Ω NORMAL CASE 5V: R = (5V - 3.3V) / 0.005A R = 1.7V / 0.005A R = 340Ω
5V SOURCE AUTOSELECT
5V ±3% REGULATED WITH LOW NOISE
RECOMMENDED VALUE AS PER SUBSEQUENT REGULATOR DATASHEET, MISSING ON PRIOR PCB.
SMALL HIGH CURRENT INDUCTOR
BOTH EARLY STAGE POWER FOR THE TUSB321 CHIP TO SUPPORT USB POWER DISTRIBUTION NEGOTIATION AND THE LATER STAGE HIGHER CURRENT SUPPLY

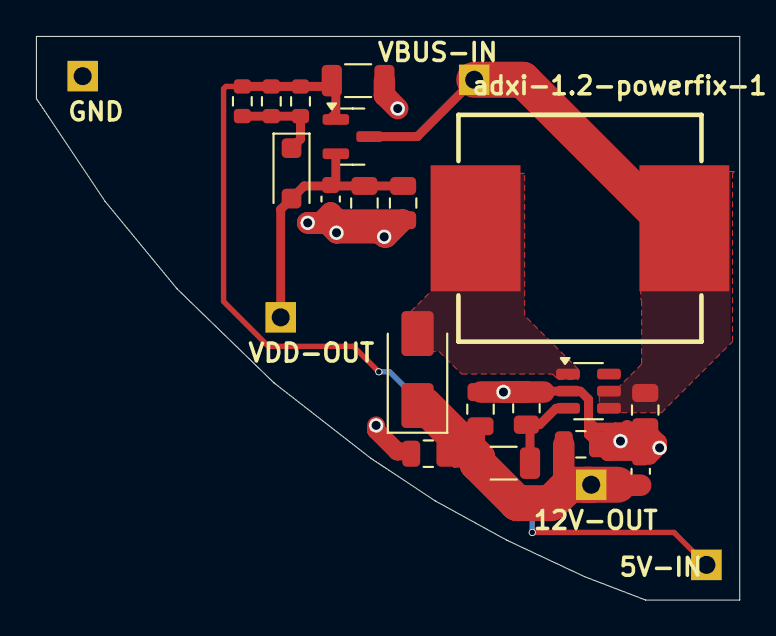
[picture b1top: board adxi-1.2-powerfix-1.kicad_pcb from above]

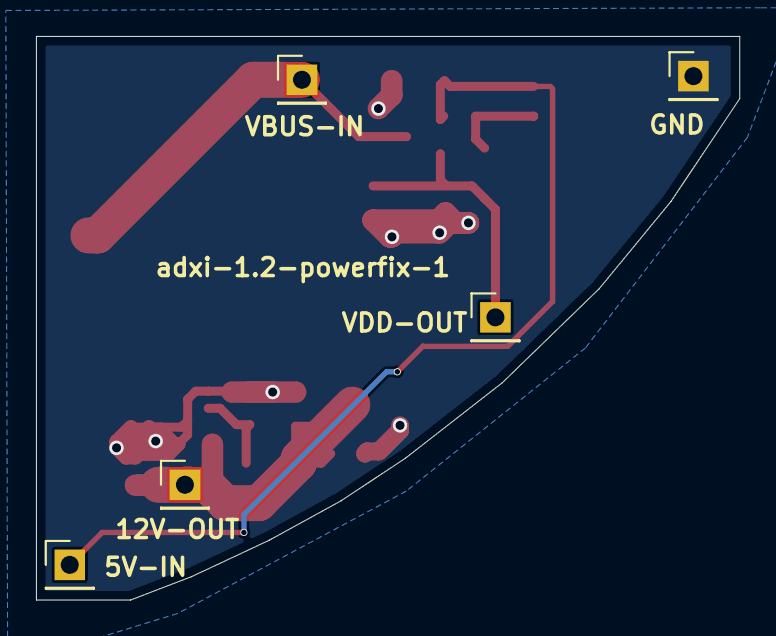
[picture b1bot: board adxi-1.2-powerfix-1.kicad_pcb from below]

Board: 2 copper layers, 39.1 x 31.3 mm, 24 parts (5 on the bottom side), 8 nets.
